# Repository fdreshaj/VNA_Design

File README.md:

# VNA_Design
Work in Progress Design of a VNA 

The Subsystems and Simulations folder contains all files related to the research and pre fabrication testing/simulations of subsystems

VNA_Project folder contains all KiCad files of the board itself. Specifically open VNA_Project.kicad_pro to check out the design. KiCad files do not have RF subsystem layout as that will be done in ADS during testing.

Motherboard Layout

Stackup:

3D+Layer View:

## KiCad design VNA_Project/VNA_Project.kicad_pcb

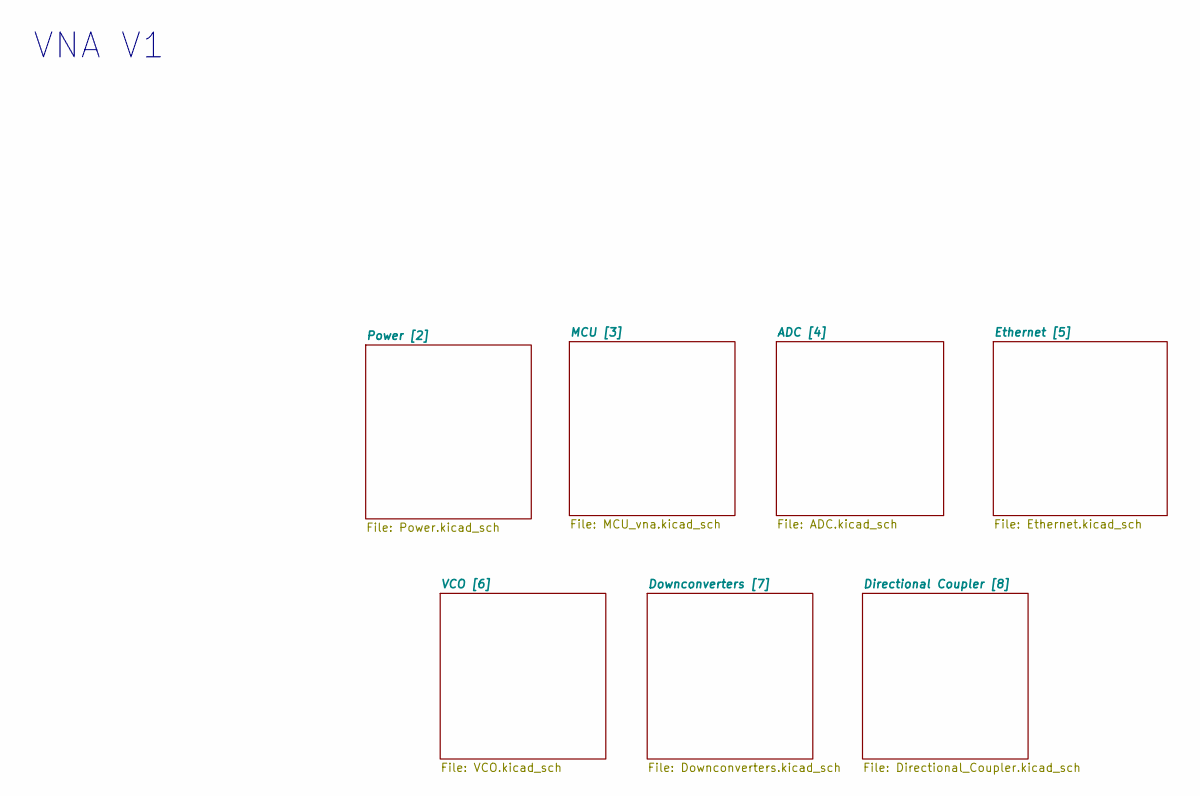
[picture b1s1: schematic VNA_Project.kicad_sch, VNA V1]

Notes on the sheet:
VNA V1

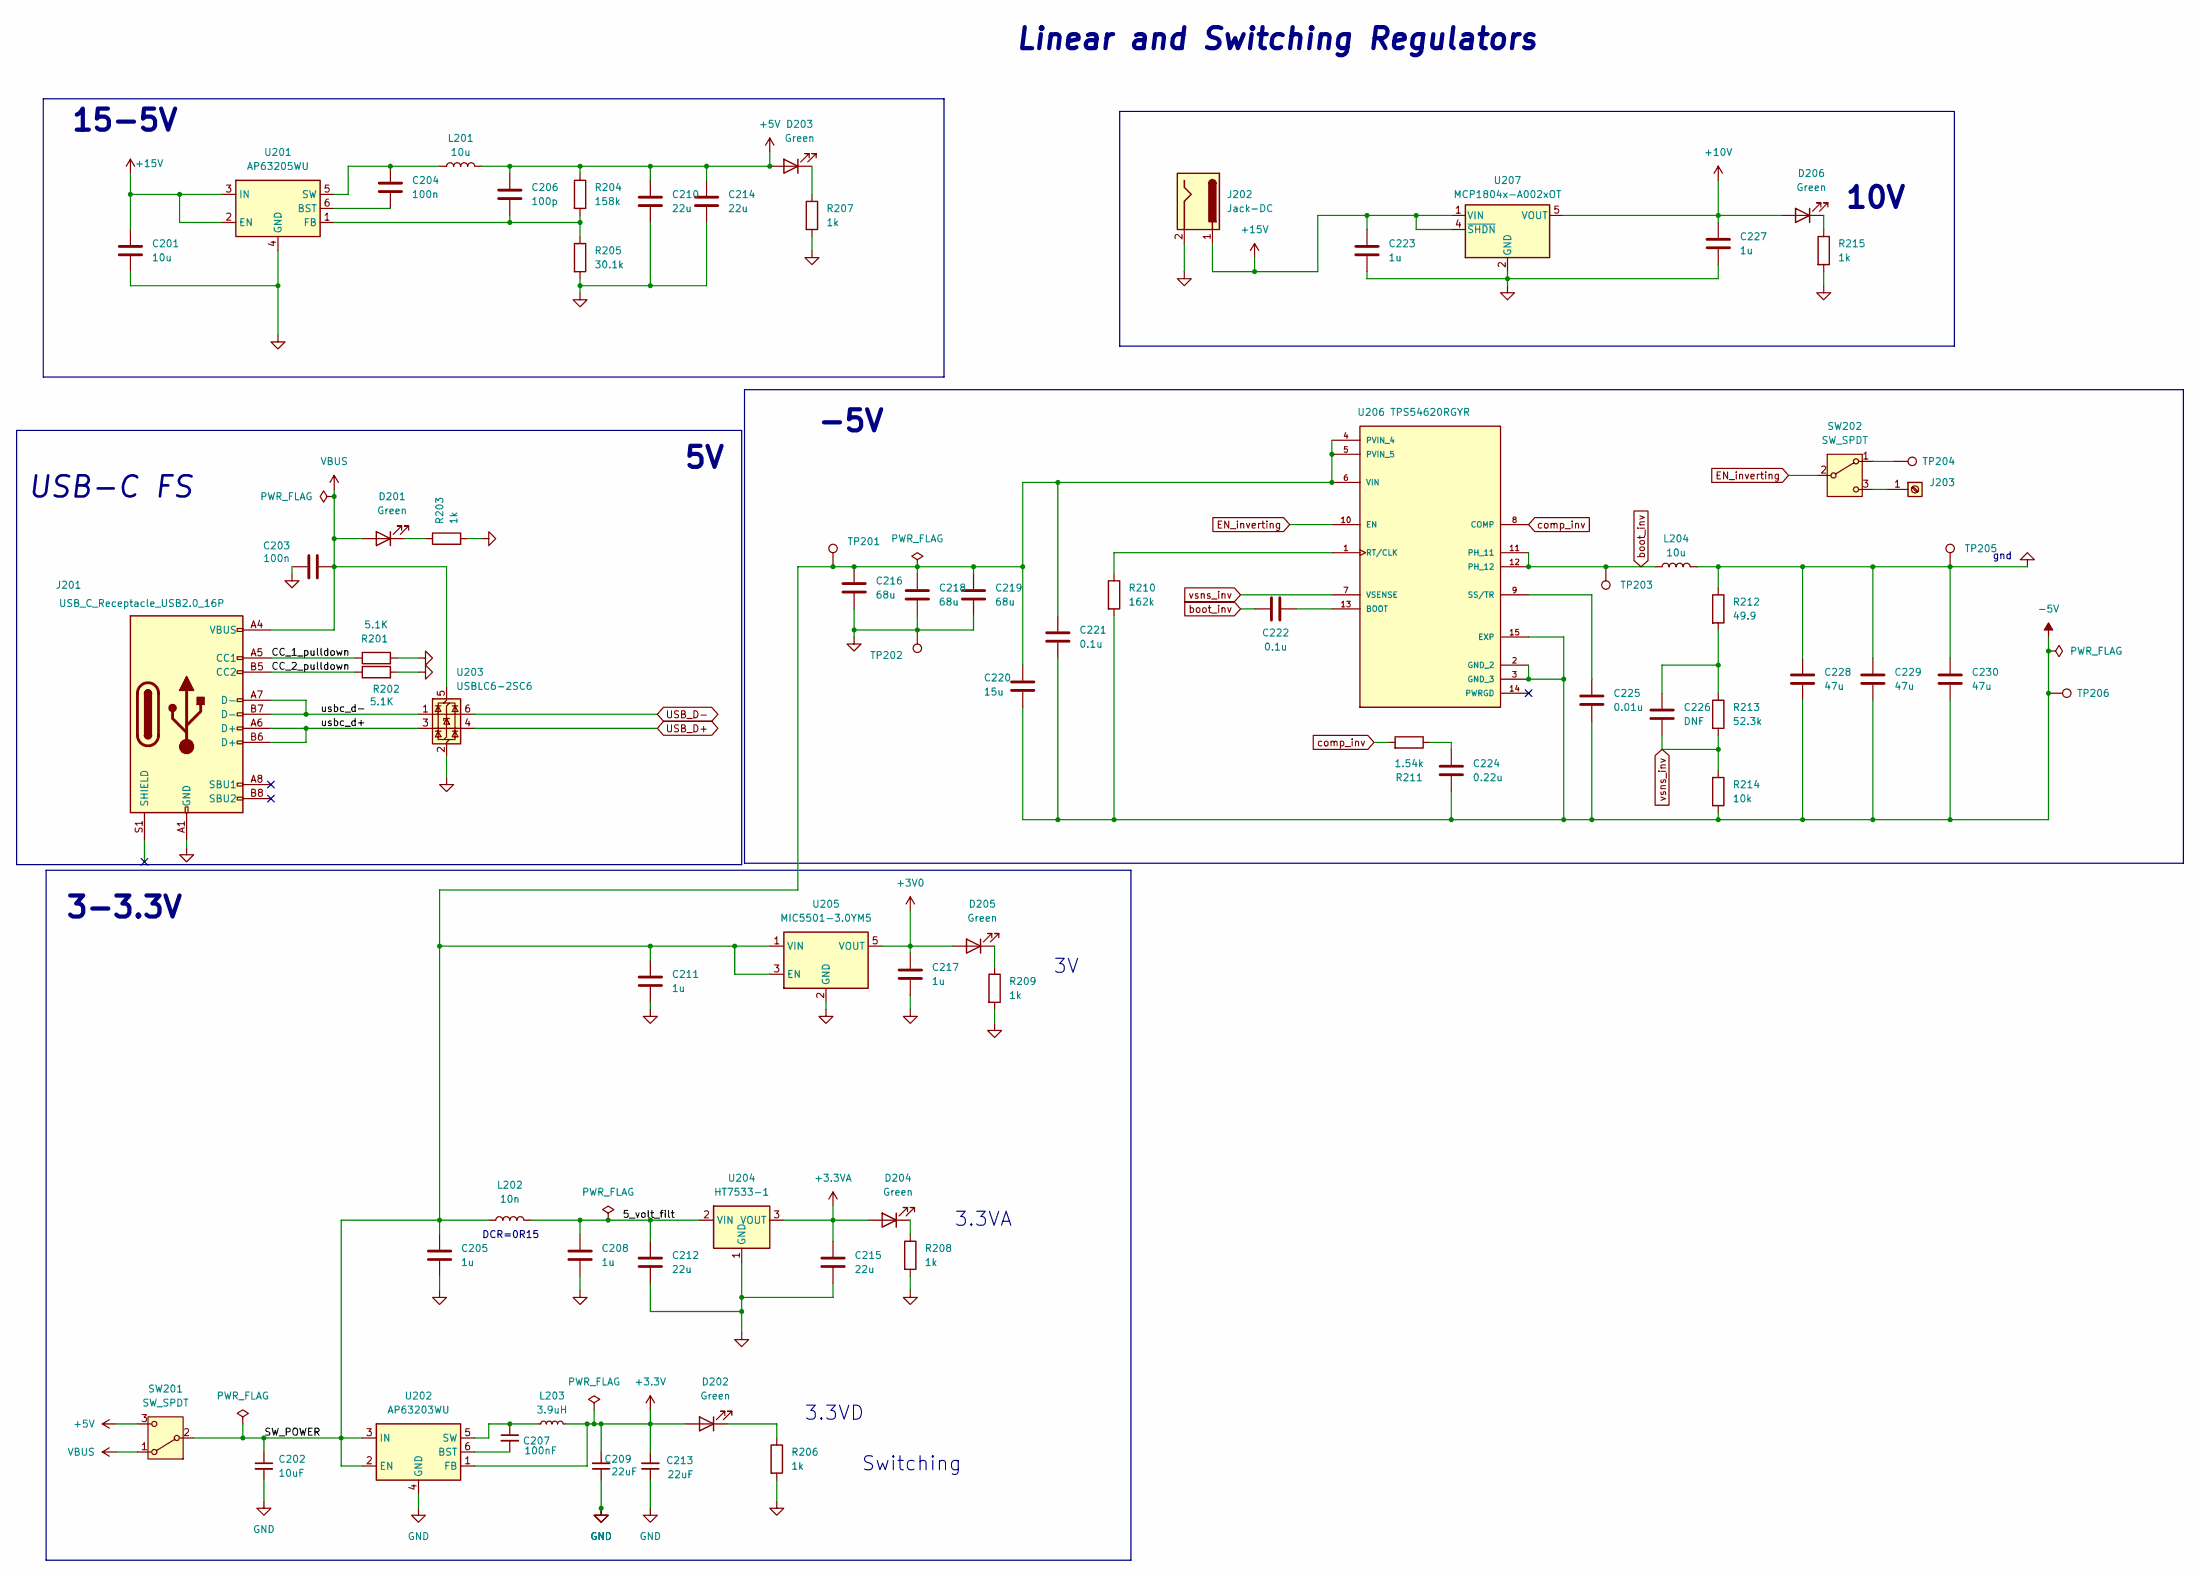
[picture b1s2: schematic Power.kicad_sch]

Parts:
C201: 10u; C_0805_2012Metric
C202: 10uF; C_0805_2012Metric
C203, C204: 100n; C_0603_1608Metric
C205, C208, C211, C217, C223, C227: 1u; C_0805_2012Metric
C206: 100p; C_0805_2012Metric
C207: 100nF; C_0603_1608Metric
C209, C213: 22uF; C_0805_2012Metric
C210, C212, C214, C215: 22u; C_0805_2012Metric
C216, C218, C219: 68u; C_0805_2012Metric
C220: 15u; C_0805_2012Metric
C221, C222: 0.1u; C_0603_1608Metric
C224: 0.22u; C_0805_2012Metric
C225: 0.01u; C_0805_2012Metric
C226: DNF; C_0805_2012Metric
C228, C229, C230: 47u; C_0805_2012Metric
D201, D202, D203, D204, D205, D206: Green; LED_0603_1608Metric_Pad1.05x0.95mm_HandSolder
J201: USB_C_Receptacle_USB2.0_16P; USB_C_Receptacle_G-Switch_GT-USB-7010ASV
J202: Jack-DC; BarrelJack_GCT_DCJ200-10-A_Horizontal
J203: Screw_Terminal_01x01; TerminalBlock_MaiXu_MX126-5.0-02P_1x02_P5.00mm
L201, L204: 10u; L_APV_ANR6020
L202: 10n; L_APV_ANR6020
L203: 3.9uH; L_APV_ANR6020
R201, R202: 5.1K; R_0603_1608Metric_Pad0.98x0.95mm_HandSolder
R203, R206, R207, R208, R209, R215: 1k; R_0603_1608Metric_Pad0.98x0.95mm_HandSolder
R204: 158k; R_0603_1608Metric_Pad0.98x0.95mm_HandSolder
R205: 30.1k; R_0603_1608Metric_Pad0.98x0.95mm_HandSolder
R210: 162k; R_0603_1608Metric_Pad0.98x0.95mm_HandSolder
R211: 1.54k; R_0603_1608Metric_Pad0.98x0.95mm_HandSolder
R212: 49.9; R_0603_1608Metric_Pad0.98x0.95mm_HandSolder
R213: 52.3k; R_0603_1608Metric_Pad0.98x0.95mm_HandSolder
R214: 10k; R_0603_1608Metric_Pad0.98x0.95mm_HandSolder
SW201, SW202: SW_SPDT; SW_Slide_SPDT_Straight_CK_OS102011MS2Q
TP201, TP202, TP203, TP204, TP205, TP206: TestPoint; TestPoint_Pad_D4.0mm
U201: AP63205WU; TSOT-23-6_HandSoldering
U202: AP63203WU; TSOT-23-6_HandSoldering
U203: USBLC6-2SC6; SOT-23-6_Handsoldering
U204: HT7533-1; SOT-89-3_Handsoldering
U205: MIC5501-3.0YM5; SOT-23-5_HandSoldering
U206: TPS54620RGYR; PARTREV 06/2011
U207: MCP1804x-A002xOT; SOT-23-5_HandSoldering

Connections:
+3.3V: C209.2, C213.2, D202.2 (A), L203.2, U202.1 (FB); also elsewhere on the board
+3.3VA: C215.1, D204.2 (A), U204.3 (VOUT); also elsewhere on the board
+3V0: C217.1, D205.2 (A), U205.5 (VOUT); also elsewhere on the board
+5V: C206.1, C210.1, C214.1, D203.2 (A), L201.2, R204.1, SW201.3 (C); also elsewhere on the board
+10V: C227.1, D206.2 (A), U207.5 (VOUT); also elsewhere on the board
+15V: C201.1, C223.1, J202.1, U201.2 (EN), U201.3 (IN), U207.1 (VIN), U207.4 (~SHDN)
-5V: C220.2, C221.2, C224.2, C225.2, C228.2, C229.2, C230.2, R210.2, R214.2, TP206.1, U206.2 (GND_2), U206.3 (GND_3), U206.15 (EXP); also elsewhere on the board
/Power [2]/5_volt_filt: C208.1, C212.1, L202.2, U204.2 (VIN)
/Power [2]/CC_1_pulldown: J201.A5 (CC1), R201.1
/Power [2]/CC_2_pulldown: J201.B5 (CC2), R202.1
/Power [2]/SW_POWER: C202.1, C205.1, C211.1, C216.1, C218.1, C219.1, C220.1, C221.1, L202.1, SW201.2 (B), TP201.1, U202.2 (EN), U202.3 (IN), U205.1 (VIN), U205.3 (EN), U206.4 (PVIN_4), U206.5 (PVIN_5), U206.6 (VIN)
/Power [2]/usbc_d+: J201.A6 (D+), J201.B6 (D+), U203.3 (I/O2)
/Power [2]/usbc_d-: J201.A7 (D-), J201.B7 (D-), U203.1 (I/O1)
EN_inverting: SW202.2 (B), U206.10 (EN)
GND: C201.2, C202.2, C203.1, C205.2, C208.2, C209.1, C210.2, C211.2, C212.2, C213.1, C214.2, C215.2, C216.2, C217.2, C218.2, C219.2, C223.2, C227.2, C228.1, C229.1, C230.1, J201.A1 (GND), J201.A12 (GND), J201.B1 (GND), J201.B12 (GND), J202.2, L204.2, R201.2, R202.2, R203.2, R205.2, R206.2, R207.2, R208.2, R209.2, R212.1, R215.2, TP202.1, TP205.1, U201.4 (GND), U202.4 (GND), U203.2 (GND), U204.1 (GND), U205.2 (GND), U207.2 (GND); also elsewhere on the board
unnamed: C224.1, R211.1
unnamed: C226.1, R212.2, R213.1
unnamed: D201.1 (K), R203.1
unnamed: D202.1 (K), R206.1
unnamed: D203.1 (K), R207.1
unnamed: D204.1 (K), R208.1
unnamed: D205.1 (K), R209.1
unnamed: D206.1 (K), R215.1
unnamed: J203.1, SW202.3 (C)
unnamed: SW202.1 (A), TP204.1
unnamed: C204.2, U201.6 (BST)
unnamed: C206.2, R204.2, R205.1, U201.1 (FB)
unnamed: C204.1, L201.1, U201.5 (SW)
unnamed: C207.2, U202.6 (BST)
unnamed: C207.1, L203.1, U202.5 (SW)
unnamed: C222.2, U206.13 (BOOT)
unnamed: R210.1, U206.1 (RT/CLK)
unnamed: C225.1, U206.9 (SS/TR)
USB_D+: U203.4 (I/O2); also elsewhere on the board
USB_D-: U203.6 (I/O1); also elsewhere on the board
VBUS: C203.2, D201.2 (A), J201.A4 (VBUS), J201.A9 (VBUS), J201.B4 (VBUS), J201.B9 (VBUS), SW201.1 (A), U203.5 (VBUS)
boot_inv: C222.1, L204.1, TP203.1, U206.11 (PH_11), U206.12 (PH_12)
comp_inv: R211.2, U206.8 (COMP)
vsns_inv: C226.2, R213.2, R214.1, U206.7 (VSENSE)

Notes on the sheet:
Switching
DCR=0R15
Linear and Switching Regulators
3.3VD
gnd
10V
3.3VA
-5V
3-3.3V
15-5V
USB-C FS

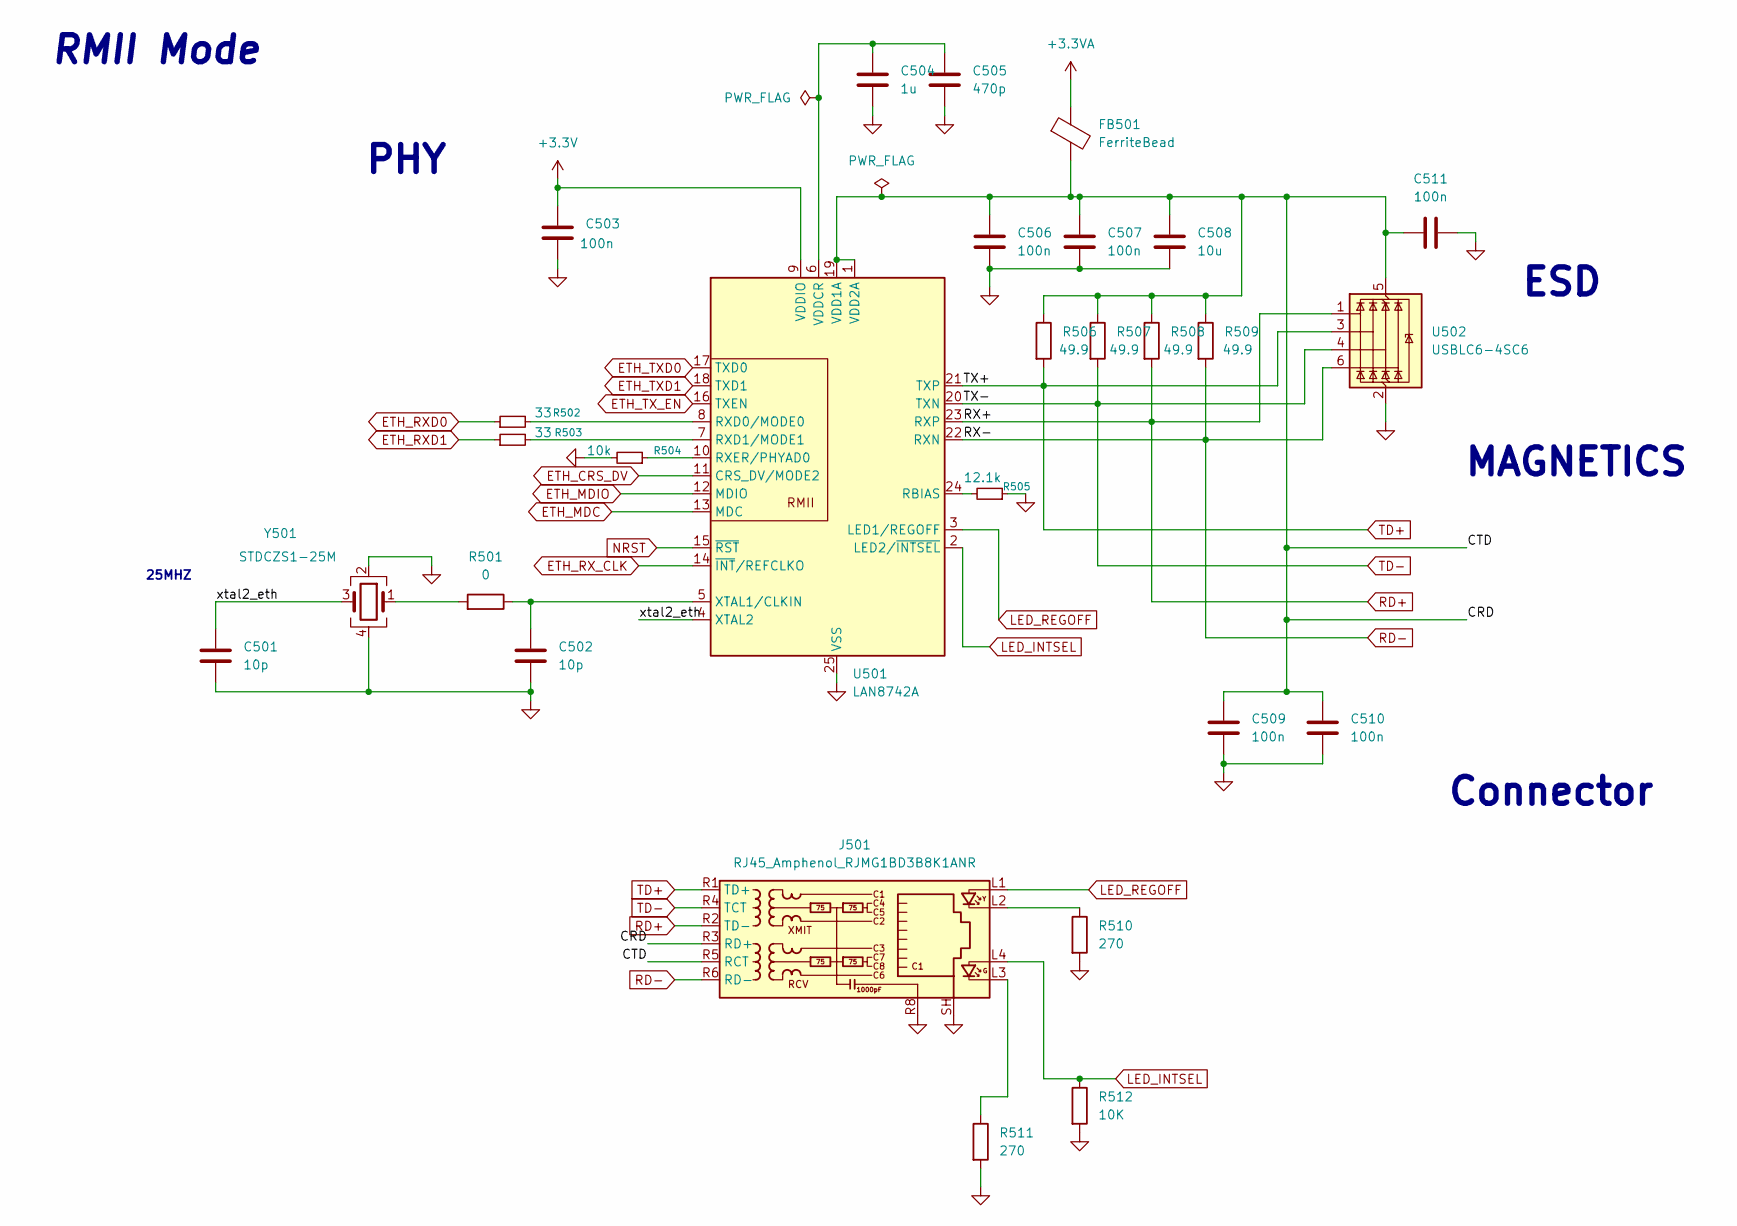
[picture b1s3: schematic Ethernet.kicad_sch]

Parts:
C501, C502: 10p; C_0603_1608Metric_Pad1.08x0.95mm_HandSolder
C503, C506, C507, C509, C510, C511: 100n; C_0603_1608Metric_Pad1.08x0.95mm_HandSolder
C504: 1u; C_0603_1608Metric_Pad1.08x0.95mm_HandSolder
C505: 470p; C_0603_1608Metric_Pad1.08x0.95mm_HandSolder
C508: 10u; C_0603_1608Metric_Pad1.08x0.95mm_HandSolder
FB501: FerriteBead; L_0603_1608Metric_Pad1.05x0.95mm_HandSolder
J501: RJ45_Amphenol_RJMG1BD3B8K1ANR
R501: 0; R_0603_1608Metric_Pad0.98x0.95mm_HandSolder
R502, R503: 33; R_0603_1608Metric_Pad0.98x0.95mm_HandSolder
R504: 10k; R_0603_1608Metric_Pad0.98x0.95mm_HandSolder
R505: 12.1k; R_0603_1608Metric_Pad0.98x0.95mm_HandSolder
R506, R507, R508, R509: 49.9; R_0603_1608Metric_Pad0.98x0.95mm_HandSolder
R510, R511: 270; R_0603_1608Metric_Pad0.98x0.95mm_HandSolder
R512: 10K; R_0603_1608Metric_Pad0.98x0.95mm_HandSolder
U501: LAN8742A; VQFN-24-1EP_4x4mm_P0.5mm_EP2.5x2.5mm
U502: USBLC6-4SC6; SOT-23-6_Handsoldering
Y501: STDCZS1-25M; Crystal_SMD_2016-4Pin_2.0x1.6mm

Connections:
+3.3V: C503.1, U501.9 (VDDIO); also elsewhere on the board
+3.3VA: FB501.1; also elsewhere on the board
/Ethernet [5]/CRD: C506.1, C507.1, C508.1, C509.1, C510.1, C511.1, FB501.2, J501.R3 (RD+), J501.R5 (RCT), R506.1, R507.1, R508.1, R509.1, U501.1 (VDD2A), U501.19 (VDD1A), U502.5 (VBUS)
/Ethernet [5]/xtal2_eth: C501.1, U501.4 (XTAL2), Y501.3
ETH_CRS_DV: U501.11 (CRS_DV/MODE2); also elsewhere on the board
ETH_MDC: U501.13 (MDC); also elsewhere on the board
ETH_MDIO: U501.12 (MDIO); also elsewhere on the board
ETH_RXD0: R502.1; also elsewhere on the board
ETH_RXD1: R503.1; also elsewhere on the board
ETH_RX_CLK: U501.14 (~INT/REFCLKO); also elsewhere on the board
ETH_TXD0: U501.17 (TXD0); also elsewhere on the board
ETH_TXD1: U501.18 (TXD1); also elsewhere on the board
ETH_TX_EN: U501.16 (TXEN); also elsewhere on the board
GND: C501.2, C502.2, C503.2, C504.2, C505.2, C506.2, C507.2, C508.2, C509.2, C510.2, C511.2, J501.R8, J501.SH, R504.2, R505.1, R510.2, R511.2, R512.2, U501.25 (VSS), U502.2 (GND), Y501.2, Y501.4; also elsewhere on the board
LED_INTSEL: J501.L4, R512.1, U501.2 (LED2/~INTSEL)
LED_REGOFF: J501.L1, U501.3 (LED1/REGOFF)
NRST: U501.15 (~RST); also elsewhere on the board
unnamed: J501.L2, R510.1
unnamed: J501.L3, R511.1
unnamed: R501.2, Y501.1
unnamed: R505.2, U501.24 (RBIAS)
unnamed: R502.2, U501.8 (RXD0/MODE0)
unnamed: R503.2, U501.7 (RXD1/MODE1)
unnamed: R504.1, U501.10 (RXER/PHYAD0)
unnamed: C504.1, C505.1, U501.6 (VDDCR)
unnamed: C502.1, R501.1, U501.5 (XTAL1/CLKIN)
RD+: J501.R2 (TD-), R508.2, U501.23 (RXP), U502.1 (I/O1)
RD-: J501.R6 (RD-), R509.2, U501.22 (RXN), U502.6 (I/O4)
TD+: J501.R1 (TD+), R506.2, U501.21 (TXP), U502.3 (I/O2)
TD-: J501.R4 (TCT), R507.2, U501.20 (TXN), U502.4 (I/O3)

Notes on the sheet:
MAGNETICS
Connector
25MHZ
RMII Mode
ESD
PHY

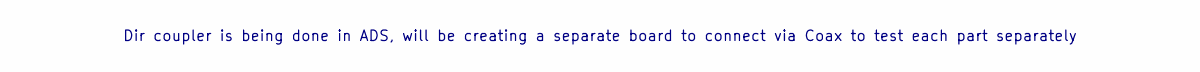
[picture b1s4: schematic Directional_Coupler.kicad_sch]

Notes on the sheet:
Dir coupler is being done in ADS, will be creating a separate board to connect via Coax to test each part separately

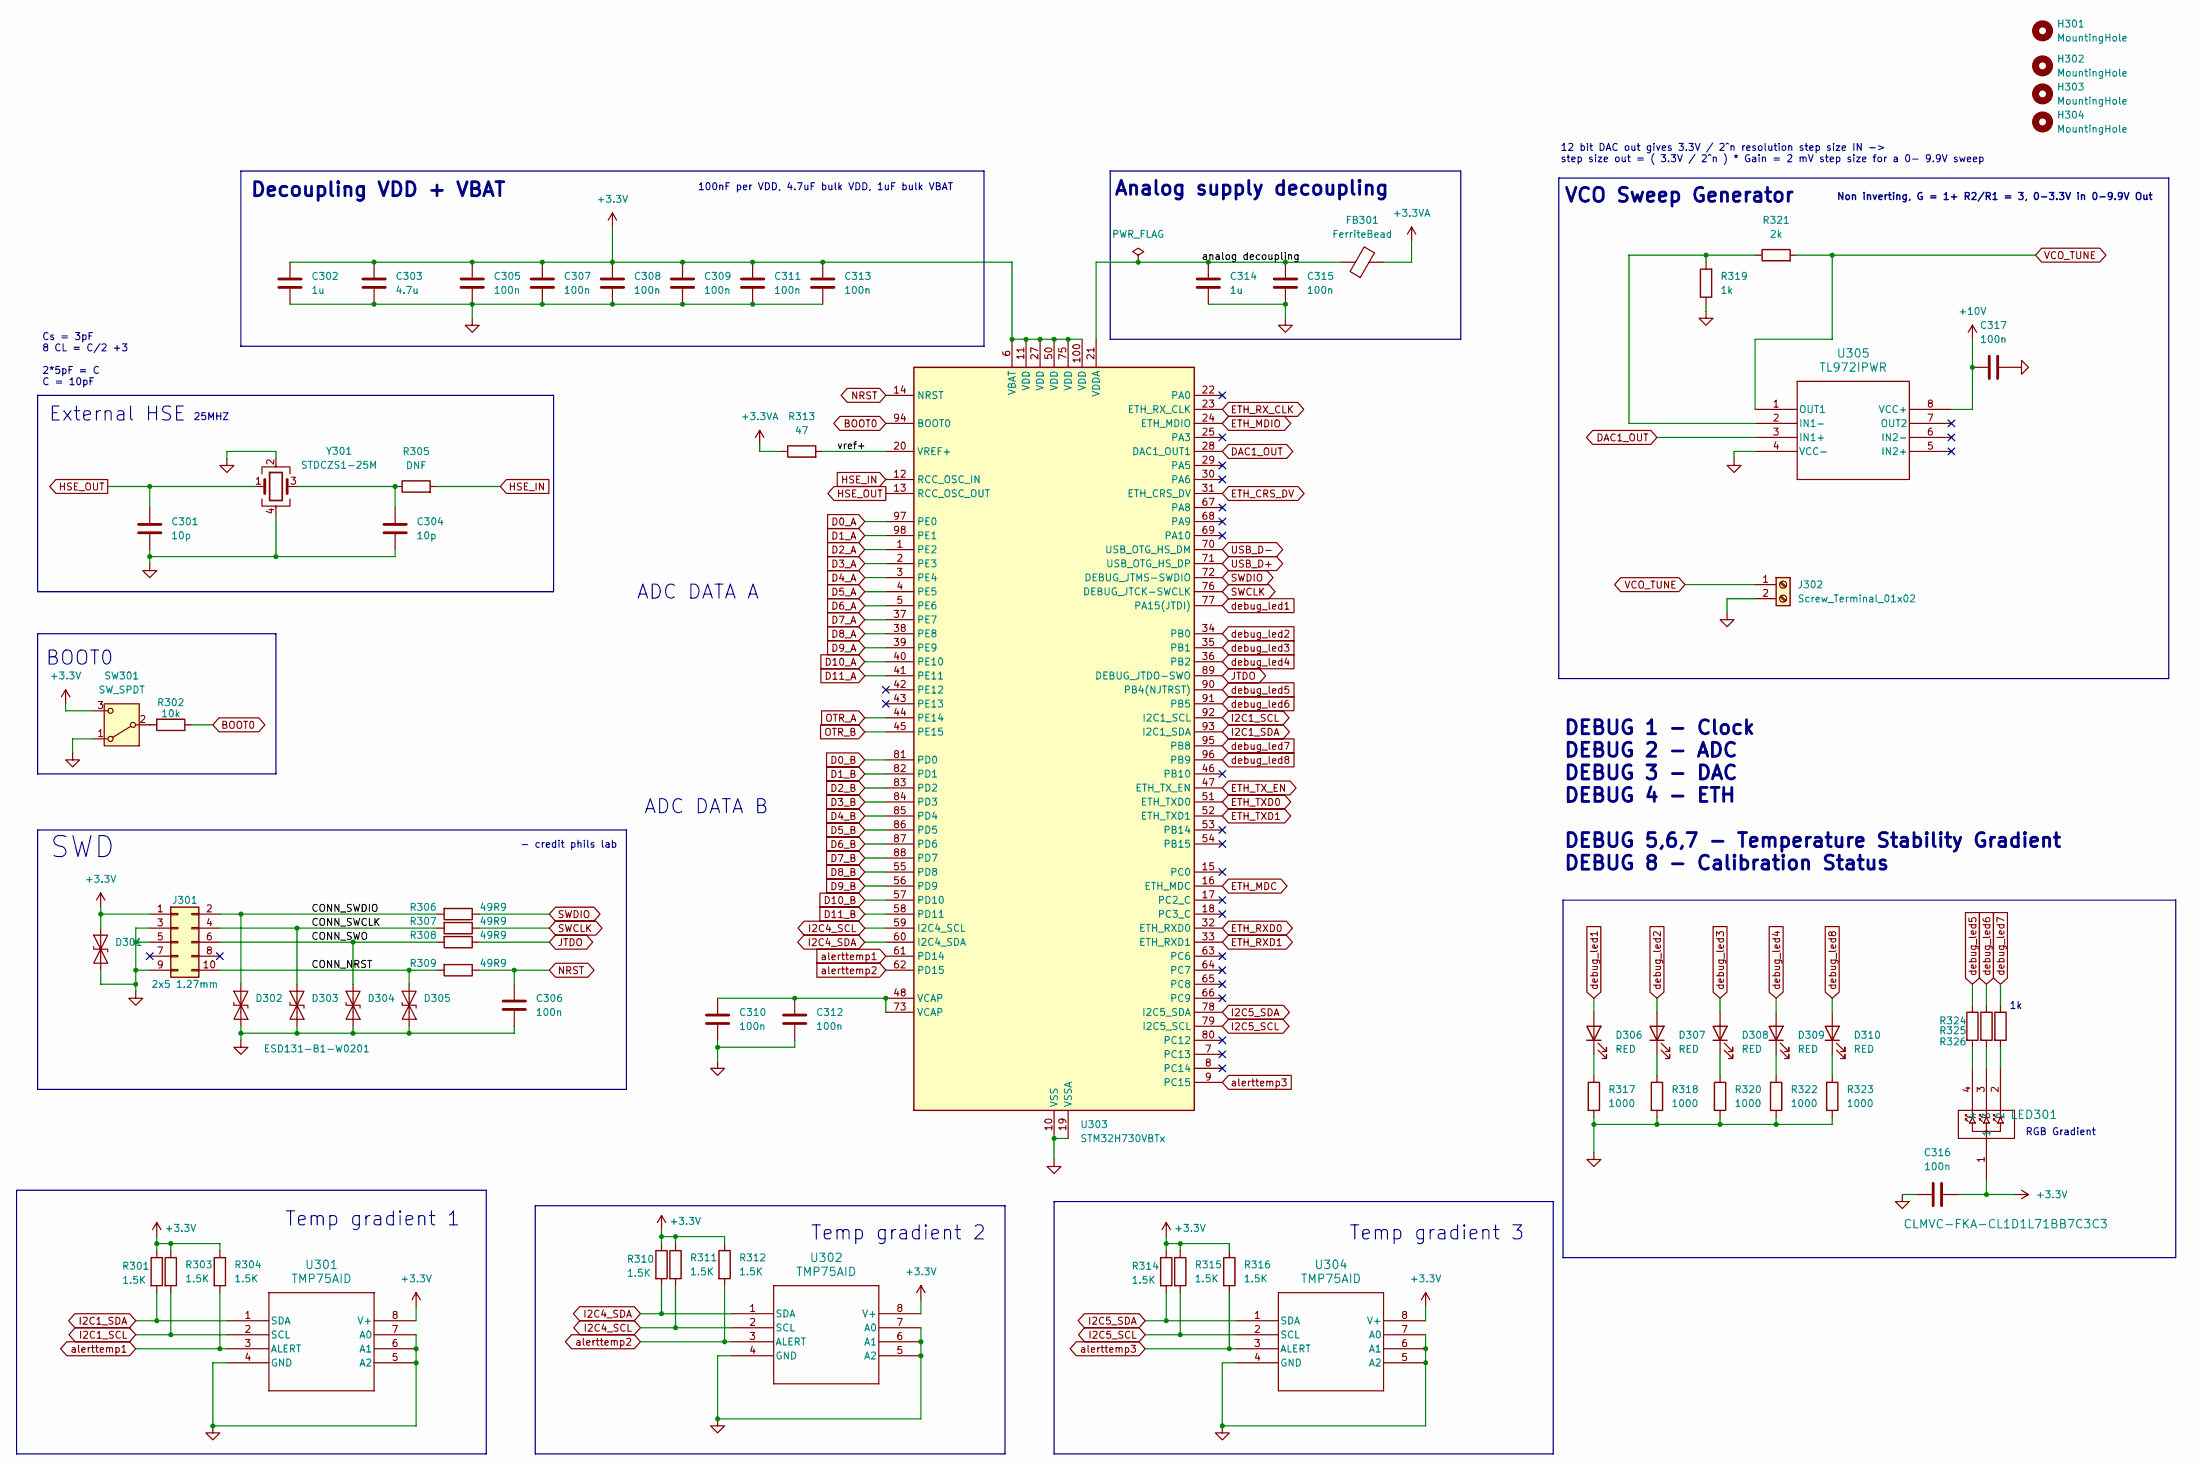
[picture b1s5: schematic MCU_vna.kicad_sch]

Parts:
C301, C304: 10p; C_0603_1608Metric_Pad1.08x0.95mm_HandSolder
C302, C314: 1u; C_0603_1608Metric_Pad1.08x0.95mm_HandSolder
C303: 4.7u; C_0603_1608Metric_Pad1.08x0.95mm_HandSolder
C305, C306, C307, C308, C309, C310, C311, C312, C313, C315, C316, C317: 100n; C_0603_1608Metric_Pad1.08x0.95mm_HandSolder
D301, D302, D303, D304, D305: ESD131-B1-W0201; Nexperia_DSN0603-2_0.6x0.3mm_P0.4mm
D306, D307, D308, D309, D310: RED; LED_0603_1608Metric_Pad1.05x0.95mm_HandSolder
FB301: FerriteBead; L_0603_1608Metric_Pad1.05x0.95mm_HandSolder
H301, H302, H303, H304: MountingHole; MountingHole_2.2mm_M2
J301: 2x5 1.27mm; PinHeader_2x05_P2.54mm_Vertical
J302: Screw_Terminal_01x02; TerminalBlock_MaiXu_MX126-5.0-02P_1x02_P5.00mm
LED301: CLMVC-FKA-CL1D1L71BB7C3C3; CLMVC-FKA-CL1D1L71BB7C3C3_CRE
R301, R303, R304, R310, R311, R312, R314, R315, R316: 1.5K; R_0603_1608Metric_Pad0.98x0.95mm_HandSolder
R302: 10k; R_0603_1608Metric_Pad0.98x0.95mm_HandSolder
R305: DNF; R_0603_1608Metric_Pad0.98x0.95mm_HandSolder
R306, R307, R308, R309: 49R9; R_0603_1608Metric_Pad0.98x0.95mm_HandSolder
R313: 47; R_0603_1608Metric_Pad0.98x0.95mm_HandSolder
R317, R318, R320, R322, R323, R324, R325, R326: 1000; R_0603_1608Metric_Pad0.98x0.95mm_HandSolder
R319: 1k; R_0603_1608Metric_Pad0.98x0.95mm_HandSolder
R321: 2k; R_0603_1608Metric_Pad0.98x0.95mm_HandSolder
SW301: SW_SPDT; SW_Slide_SPDT_Straight_CK_OS102011MS2Q
U301, U302, U304: TMP75AID
U303: STM32H730VBTx; LQFP-100_14x14mm_P0.5mm
U305: TL972IPWR
Y301: STDCZS1-25M; Crystal_SMD_2016-4Pin_2.0x1.6mm

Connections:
+3.3V: C302.1, C303.1, C305.1, C307.1, C308.1, C309.1, C311.1, C313.1, C316.1, D301.2 (A2), J301.1, LED301.1, R301.1, R303.1, R304.1, R310.1, R311.1, R312.1, R314.1, R315.1, R316.1, SW301.3 (C), U301.8 (V+), U302.8 (V+), U303.6 (VBAT), U303.11 (VDD), U303.27 (VDD), U303.50 (VDD), U303.75 (VDD), U303.100 (VDD), U304.8 (V+); also elsewhere on the board
+3.3VA: FB301.2, R313.1; also elsewhere on the board
+10V: C317.1, U305.8 (VCC+); also elsewhere on the board
/MCU [3]/CONN_NRST: D305.2 (A2), J301.10, R309.2
/MCU [3]/CONN_SWCLK: D303.2 (A2), J301.4, R307.2
/MCU [3]/CONN_SWDIO: D302.2 (A2), J301.2, R306.2
/MCU [3]/CONN_SWO: D304.2 (A2), J301.6, R308.2
/MCU [3]/analog decoupling: C314.1, C315.1, FB301.1, U303.21 (VDDA)
/MCU [3]/vref+: R313.2, U303.20 (VREF+)
BOOT0: R302.1, U303.94 (BOOT0)
D0_A: U303.97 (PE0); also elsewhere on the board
D0_B: U303.81 (PD0); also elsewhere on the board
D1_A: U303.98 (PE1); also elsewhere on the board
D1_B: U303.82 (PD1); also elsewhere on the board
D2_A: U303.1 (PE2); also elsewhere on the board
D2_B: U303.83 (PD2); also elsewhere on the board
D3_A: U303.2 (PE3); also elsewhere on the board
D3_B: U303.84 (PD3); also elsewhere on the board
D4_A: U303.3 (PE4); also elsewhere on the board
D4_B: U303.85 (PD4); also elsewhere on the board
D5_A: U303.4 (PE5); also elsewhere on the board
D5_B: U303.86 (PD5); also elsewhere on the board
D6_A: U303.5 (PE6); also elsewhere on the board
D6_B: U303.87 (PD6); also elsewhere on the board
D7_A: U303.37 (PE7); also elsewhere on the board
D7_B: U303.88 (PD7); also elsewhere on the board
D8_A: U303.38 (PE8); also elsewhere on the board
D8_B: U303.55 (PD8); also elsewhere on the board
D9_A: U303.39 (PE9); also elsewhere on the board
D9_B: U303.56 (PD9); also elsewhere on the board
D10_A: U303.40 (PE10); also elsewhere on the board
D10_B: U303.57 (PD10); also elsewhere on the board
D11_A: U303.41 (PE11); also elsewhere on the board
D11_B: U303.58 (PD11); also elsewhere on the board
DAC1_OUT: U303.28 (DAC1_OUT1), U305.3 (IN1+)
ETH_CRS_DV: U303.31 (ETH_CRS_DV); also elsewhere on the board
ETH_MDC: U303.16 (ETH_MDC); also elsewhere on the board
ETH_MDIO: U303.24 (ETH_MDIO); also elsewhere on the board
ETH_RXD0: U303.32 (ETH_RXD0); also elsewhere on the board
ETH_RXD1: U303.33 (ETH_RXD1); also elsewhere on the board
ETH_RX_CLK: U303.23 (ETH_RX_CLK); also elsewhere on the board
ETH_TXD0: U303.51 (ETH_TXD0); also elsewhere on the board
ETH_TXD1: U303.52 (ETH_TXD1); also elsewhere on the board
ETH_TX_EN: U303.47 (ETH_TX_EN); also elsewhere on the board
GND: C301.2, C302.2, C303.2, C304.2, C305.2, C306.2, C307.2, C308.2, C309.2, C310.2, C311.2, C312.2, C313.2, C314.2, C315.2, C316.2, C317.2, D301.1 (A1), D302.1 (A1), D303.1 (A1), D304.1 (A1), D305.1 (A1), J301.3, J301.5, J301.9, J302.2, R317.2, R318.2, R319.1, R320.2, R322.2, R323.2, SW301.1 (A), U301.4 (GND), U301.5 (A2), U301.6 (A1), U301.7 (A0), U302.4 (GND), U302.5 (A2), U302.6 (A1), U302.7 (A0), U303.10 (VSS), U303.19 (VSSA), U303.26 (VSS), U303.49 (VSS), U303.74 (VSS), U303.99 (VSS), U304.4 (GND), U304.5 (A2), U304.6 (A1), U304.7 (A0), U305.4 (VCC-), Y301.2, Y301.4; also elsewhere on the board
HSE_IN: R305.2, U303.12 (RCC_OSC_IN)
HSE_OUT: C301.1, U303.13 (RCC_OSC_OUT), Y301.1
I2C1_SCL: R303.2, U301.2 (SCL), U303.92 (I2C1_SCL)
I2C1_SDA: R301.2, U301.1 (SDA), U303.93 (I2C1_SDA)
I2C4_SCL: R311.2, U302.2 (SCL), U303.59 (I2C4_SCL)
I2C4_SDA: R310.2, U302.1 (SDA), U303.60 (I2C4_SDA)
I2C5_SCL: R315.2, U303.79 (I2C5_SCL), U304.2 (SCL)
I2C5_SDA: R314.2, U303.78 (I2C5_SDA), U304.1 (SDA)
JTDO: R308.1, U303.89 (DEBUG_JTDO-SWO)
NRST: C306.1, R309.1, U303.14 (NRST); also elsewhere on the board
unnamed: C304.1, R305.1, Y301.3
unnamed: C310.1, C312.1, U303.48 (VCAP), U303.73 (VCAP)
unnamed: D306.1 (K), R317.1
unnamed: D307.1 (K), R318.1
unnamed: D308.1 (K), R320.1
unnamed: D309.1 (K), R322.1
unnamed: D310.1 (K), R323.1
unnamed: LED301.2, R326.2
unnamed: LED301.3, R325.2
unnamed: LED301.4, R324.2
unnamed: R302.2, SW301.2 (B)
unnamed: R319.2, R321.1, U305.2 (IN1-)
OTR_A: U303.44 (PE14); also elsewhere on the board
OTR_B: U303.45 (PE15); also elsewhere on the board
SWCLK: R307.1, U303.76 (DEBUG_JTCK-SWCLK)
SWDIO: R306.1, U303.72 (DEBUG_JTMS-SWDIO)
USB_D+: U303.71 (USB_OTG_HS_DP); also elsewhere on the board
USB_D-: U303.70 (USB_OTG_HS_DM); also elsewhere on the board
VCO_TUNE: J302.1, R321.2, U305.1 (OUT1)
alerttemp1: R304.2, U301.3 (ALERT), U303.61 (PD14)
alerttemp2: R312.2, U302.3 (ALERT), U303.62 (PD15)
alerttemp3: R316.2, U303.9 (PC15), U304.3 (ALERT)
debug_led1: D306.2 (A), U303.77 (PA15(JTDI))
debug_led2: D307.2 (A), U303.34 (PB0)
debug_led3: D308.2 (A), U303.35 (PB1)
debug_led4: D309.2 (A), U303.36 (PB2)
debug_led5: R324.1, U303.90 (PB4(NJTRST))
debug_led6: R325.1, U303.91 (PB5)
debug_led7: R326.1, U303.95 (PB8)
debug_led8: D310.2 (A), U303.96 (PB9)

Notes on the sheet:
Temp gradient 1
VCO Sweep Generator
100nF per VDD, 4.7uF bulk VDD, 1uF bulk VBAT
- credit phils lab
RGB Gradient
BOOT0
External HSE
Temp gradient 2
ADC DATA A
DEBUG 1 - Clock DEBUG 2 - ADC DEBUG 3 - DAC DEBUG 4 - ETH DEBUG 5,6,7 - Temperature Stability Gradient DEBUG 8 - Calibration Status
Analog supply decoupling
12 bit DAC out gives 3.3V / 2^n resolution step size IN -> step size out = ( 3.3V / 2^n ) * Gain = 2 mV step size for a 0- 9.9V sweep
Cs = 3pF 8 CL = C/2 +3 2*5pF = C C = 10pF
Decoupling VDD + VBAT
Temp gradient 3
Non inverting, G = 1+ R2/R1 = 3, 0-3.3V in 0-9.9V Out
ADC DATA B
25MHZ
SWD
